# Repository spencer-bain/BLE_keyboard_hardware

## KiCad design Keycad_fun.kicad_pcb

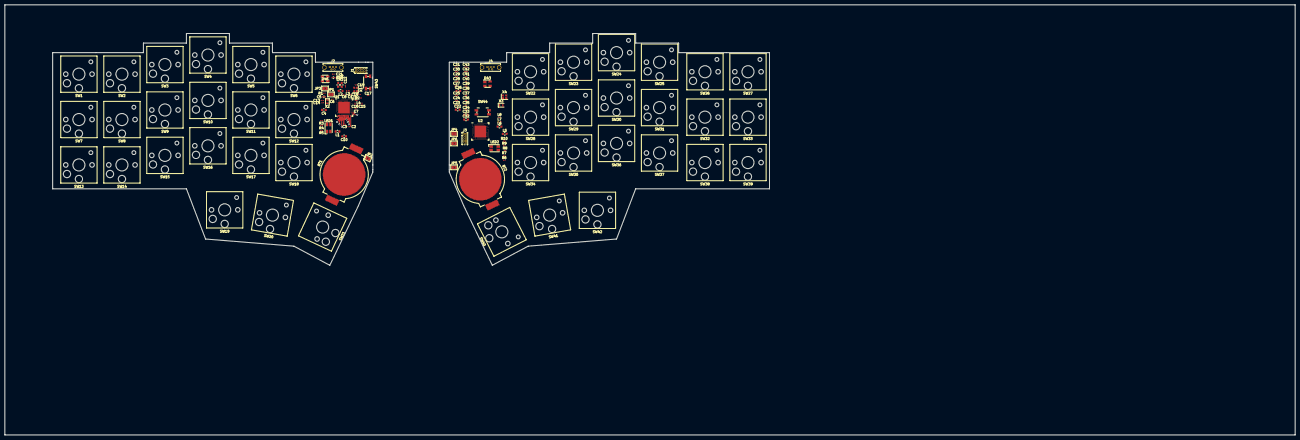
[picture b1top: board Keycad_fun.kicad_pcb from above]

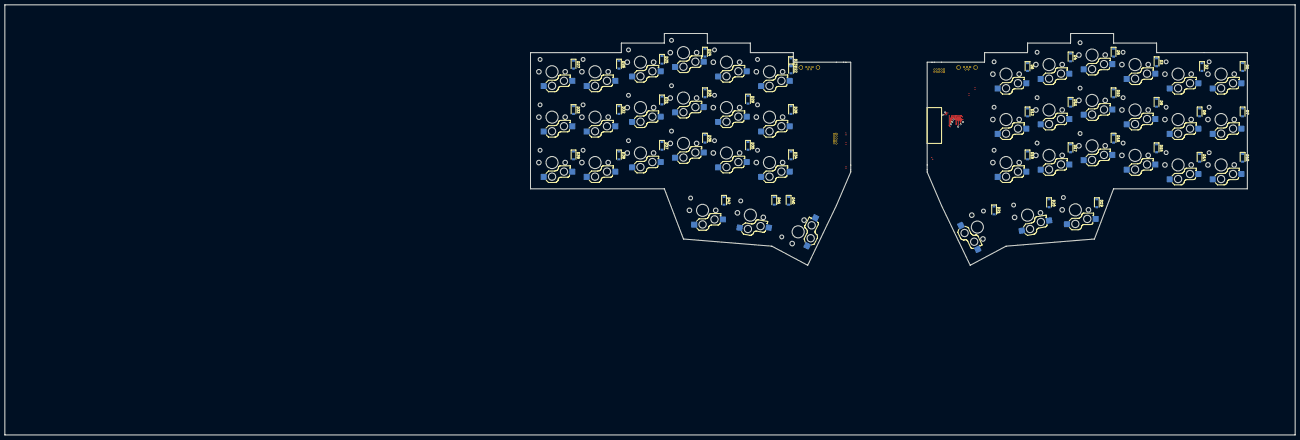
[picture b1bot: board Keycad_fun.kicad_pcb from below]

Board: 2 copper layers, 540.0 x 180.0 mm, 170 parts (42 on the bottom side), 129 nets.

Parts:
BT1, BT2: 3V; BatteryHolder_MPD_BC2003_1x2032
C0, C22: 1.0uF; C_0603_1608Metric
C1, C2, C3, C6, C17, C21, C23, C24, C25, C28, C39, C43: 100nF; C_0201_0603Metric
C4, C10, C26, C32: 4.7uF; C_0603_1608Metric
C5, C20, C27, C42: 4.7uF; C_0402_1005Metric
C7, C29: 820pF; C_0201_0603Metric
C8, C30: N.C.; C_0201_0603Metric
C9, C31: 100pF; C_0201_0603Metric
C11, C33: 1uF; C_0603_1608Metric
C12, C34: 47nF; C_0201_0603Metric
C13, C14, C18, C19, C35, C36, C40, C41: 12pF; C_0201_0603Metric
C15, C37: 0.5pF; C_0201_0603Metric
C16, C38: 0.8pF; C_0201_0603Metric
D1, D2, D3, D4, D5, D6, D7, D8, D9, D10, D11, D12, D13, D14, D15, D16, D17, D18, D19, D20, D21, D22, D23, D24, D25, D26, D27, D28, D29, D30, D31, D32, D33, D34, D35, D36, D37, D38, D39, D40, D41, D42: D; D_SOD-123
D43, D46: PRTR5V0U2X; SOT-143
J1, J3: Conn_02x05_Top_Bottom; PinHeader_2x05_P1.00mm_Vertical
J2, J4: USB_B_Micro; USB_Micro-B_Wuerth_614105150721_Vertical_CircularHoles
JP1, JP2, JP3, JP4, JP5, JP6: Jumper; SolderJumper-2_P1.3mm_Bridged2Bar_Pad1.0x1.5mm
L1, L2, L5, L6: 10uH; L_0603_1608Metric
L3, L7: 15nH; L_0402_1005Metric
L4, L8: 4.7nH; L_0201_0603Metric
LED1, LED2: ASMB-MTB0-0A3A2; LED_Avago_PLCC4_3.2x2.8mm_CW
R1, R6: 4R7; R_0201_0603Metric
R2, R10: 10k; R_0201_0603Metric
R3, R7: 1k2; R_0201_0603Metric
R4, R8: 2k2; R_0201_0603Metric
R5, R9: 390R; R_0201_0603Metric
SW1, SW2, SW3, SW4, SW5, SW6, SW7, SW8, SW9, SW10, SW11, SW12, SW13, SW14, SW15, SW16, SW17, SW18, SW19, SW20, SW21, SW22, SW23, SW24, SW25, SW26, SW27, SW28, SW29, SW30, SW31, SW32, SW33, SW34, SW35, SW36, SW37, SW38, SW39, SW40, SW41, SW42: SW_Push; SW_Hotswap_Kailh_Choc_V1V2_1.00u
SW43, SW44: SW_SPST; Panasonic_EVQPUJ_EVQPUA
U1, U2: nRF52840; Nordic_AQFN-73-1EP_7x7mm_P0.5mm
X1, X4: 32MHz; Crystal_SMD_2016-4Pin_2.0x1.6mm
X2, X3: 32.768kHz; Crystal_SMD_2012-2Pin_2.0x1.2mm

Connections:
/Col0_l: SW1.1, SW7.1, SW13.1, U1.AD8
/Col0_r: SW22.1, SW28.1, SW34.1, SW40.1, U2.AD8
/Col1_l: SW2.1, SW8.1, SW14.1, U1.AD10
/Col1_r: SW23.1, SW29.1, SW35.1, SW41.1, U2.AD10
/Col2_l: SW3.1, SW9.1, SW15.1, U1.AD12
/Col2_r: SW24.1, SW30.1, SW36.1, SW42.1, U2.AD12
/Col3_l: SW4.1, SW10.1, SW16.1, SW19.1, U1.AD16
/Col3_r: SW25.1, SW31.1, SW37.1, U2.AD16
/Col4_l: SW5.1, SW11.1, SW17.1, SW20.1, U1.AD18
/Col4_r: SW26.1, SW32.1, SW38.1, U2.AD18
/Col5_l: SW6.1, SW12.1, SW18.1, SW21.1, U1.AD20
/Col5_r: SW27.1, SW33.1, SW39.1, U2.AD20
/DCC_l: L2.2, U1.B3
/DCC_r: L6.2, U2.B3
/LED_B_l: R5.2, U1.U1
/LED_B_r: R9.2, U2.U1
/LED_G_l: R4.2, U1.R1
/LED_G_r: R8.2, U2.R1
/LED_R_l: R3.2, U1.N1
/LED_R_r: R7.2, U2.N1
/Reset_l: C17.1, R2.2, SW43.2, U1.AC13
/Reset_r: C39.1, R10.2, SW44.2, U2.AC13
/Row0_l: D1.1, D2.1, D3.1, D4.1, D5.1, D6.1, U1.L24
/Row0_r: D22.1, D23.1, D24.1, D25.1, D26.1, D27.1, U2.L24
/Row1_l: D7.1, D8.1, D9.1, D10.1, D11.1, D12.1, U1.A8
/Row1_r: D28.1, D29.1, D30.1, D31.1, D32.1, D33.1, U2.A8
/Row2_l: D13.1, D14.1, D15.1, D16.1, D17.1, D18.1, U1.A10
/Row2_r: D34.1, D35.1, D36.1, D37.1, D38.1, D39.1, U2.A10
/Row3_l: D19.1, D20.1, D21.1, U1.A12
/Row3_r: D40.1, D41.1, D42.1, U2.A12
/SWDCLK_l: J1.4, U1.AA24
/SWDCLK_r: J3.4, U2.AA24
/SWDIO_l: J1.2, U1.AC24
/SWDIO_r: J3.2, U2.AC24
/VBUS_l: C20.1, C21.1, D46.4, J1.5, JP3.2, R1.2
/VBUS_r: C42.1, C43.1, D43.4, J3.5, JP6.2, R6.2
/VDDH_l: JP1.2, U1.Y2
/VDDH_r: JP4.2, U2.Y2
/VDD_l: C0.1, C1.1, C2.1, C3.1, C4.1, JP2.2, L1.1, U1.A22, U1.AD14, U1.AD23, U1.B1, U1.W1
/VDD_r: C22.1, C23.1, C24.1, C25.1, C26.1, JP5.2, L5.1, U2.A22, U2.AD14, U2.AD23, U2.B1, U2.W1
/nrf_vcc_l: J1.1, LED1.1, R2.1
/nrf_vcc_r: J3.1, LED2.1, R10.1
GND: BT1.2, BT2.2, C0.2, C1.2, C2.2, C3.2, C4.2, C5.2, C6.1, C7.1, C8.1, C9.1, C10.1, C11.2, C12.2, C13.1, C14.1, C15.2, C16.2, C17.2, C18.2, C19.2, C20.2, C21.2, C22.2, C23.2, C24.2, C25.2, C26.2, C27.2, C28.1, C29.1, C30.1, C31.1, C32.1, C33.2, C34.2, C35.1, C36.1, C37.2, C38.2, C39.2, C40.2, C41.2, C42.2, C43.2, D43.1, D46.1, J1.3, J2.5, J3.3, J4.5, SW43.1, SW44.1, U1.B7, U1.B15, U1.EP, U1.F23, U2.B7, U2.B15, U2.EP, U2.F23, X1.2, X4.2
unnamed: BT1.1, JP2.1
unnamed: BT2.1, JP5.1
unnamed: C5.1, JP1.1, R1.1, U1.AD2
unnamed: C6.2, U1.C1
unnamed: C7.2, U1.N24
unnamed: C8.2, U1.A18
unnamed: C9.2, U1.D23
unnamed: C10.2, U1.AC5
unnamed: C11.1, L3.1, U1.B5, U1.E24
unnamed: C13.2, U1.D2, X2.1
unnamed: C14.2, U1.F2, X2.2
unnamed: C15.1, L4.1
unnamed: C16.1, L4.2, U1.H23
unnamed: C18.1, U1.B24, X1.1
unnamed: C19.1, U1.A23, X1.3
unnamed: C27.1, JP4.1, R6.1, U2.AD2
unnamed: C28.2, U2.C1
unnamed: C29.2, U2.N24
unnamed: C30.2, U2.A18
unnamed: C31.2, U2.D23
unnamed: C32.2, U2.AC5
unnamed: C33.1, L7.1, U2.B5, U2.E24
unnamed: C35.2, U2.D2, X3.1
unnamed: C36.2, U2.F2, X3.2
unnamed: C37.1, L8.1
unnamed: C38.1, L8.2, U2.H23
unnamed: C40.1, U2.B24, X4.1
unnamed: C41.1, U2.A23, X4.3
unnamed: D1.2, SW1.2
unnamed: D2.2, SW2.2
unnamed: D3.2, SW3.2
unnamed: D4.2, SW4.2
unnamed: D5.2, SW5.2
unnamed: D6.2, SW6.2
unnamed: D7.2, SW7.2
unnamed: D8.2, SW8.2
unnamed: D9.2, SW9.2
unnamed: D10.2, SW10.2
unnamed: D11.2, SW11.2
unnamed: D12.2, SW12.2
unnamed: D13.2, SW13.2
unnamed: D14.2, SW14.2
unnamed: D15.2, SW15.2
unnamed: D16.2, SW16.2
unnamed: D17.2, SW17.2
unnamed: D18.2, SW18.2
unnamed: D19.2, SW19.2
unnamed: D20.2, SW20.2
unnamed: D21.2, SW21.2
unnamed: D22.2, SW22.2
unnamed: D23.2, SW23.2
unnamed: D24.2, SW24.2
unnamed: D25.2, SW25.2
unnamed: D26.2, SW26.2
unnamed: D27.2, SW27.2
unnamed: D28.2, SW28.2
unnamed: D29.2, SW29.2
unnamed: D30.2, SW30.2
unnamed: D31.2, SW31.2
unnamed: D32.2, SW32.2
unnamed: D33.2, SW33.2
unnamed: D34.2, SW34.2
unnamed: D35.2, SW35.2
unnamed: D36.2, SW36.2
unnamed: D37.2, SW37.2
unnamed: D38.2, SW38.2
unnamed: D39.2, SW39.2
unnamed: D40.2, SW40.2
unnamed: D41.2, SW41.2
unnamed: D42.2, SW42.2
unnamed: D43.2, J4.2, U2.AD4
unnamed: D43.3, J4.3, U2.AD6
unnamed: D46.2, J2.2, U1.AD4
unnamed: D46.3, J2.3, U1.AD6
unnamed: J2.1, JP3.1
unnamed: J4.1, JP6.1
unnamed: L1.2, U1.AB2
unnamed: L2.1, L3.2
unnamed: L5.2, U2.AB2
unnamed: L6.1, L7.2
unnamed: LED1.2, R5.1
unnamed: LED1.3, R4.1
unnamed: LED1.4, R3.1
unnamed: LED2.2, R9.1
unnamed: LED2.3, R8.1
unnamed: LED2.4, R7.1

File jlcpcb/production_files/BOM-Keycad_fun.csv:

Comment,Designator,Footprint,LCSC
3V,BT1,BatteryHolder_MPD_BC2003_1x2032,
3V,BT2,BatteryHolder_MPD_BC2003_1x2032,
1.0uF,C0,C_0603_1608Metric,
100nF,C1,C_0201_0603Metric,
100nF,C2,C_0201_0603Metric,
100nF,C3,C_0201_0603Metric,
4.7uF,C4,C_0603_1608Metric,
4.7uF,C5,C_0402_1005Metric,
100nF,C6,C_0201_0603Metric,
820pF,C7,C_0201_0603Metric,
N.C.,C8,C_0201_0603Metric,
100pF,C9,C_0201_0603Metric,
4.7uF,C10,C_0603_1608Metric,
1uF,C11,C_0603_1608Metric,
47nF,C12,C_0201_0603Metric,
12pF,C13,C_0201_0603Metric,
12pF,C14,C_0201_0603Metric,
0.5pF,C15,C_0201_0603Metric,
0.8pF,C16,C_0201_0603Metric,
100nF,C17,C_0201_0603Metric,
12pF,C18,C_0201_0603Metric,
12pF,C19,C_0201_0603Metric,
4.7uF,C20,C_0402_1005Metric,
100nF,C21,C_0201_0603Metric,
1.0uF,C22,C_0603_1608Metric,
100nF,C23,C_0201_0603Metric,
100nF,C24,C_0201_0603Metric,
100nF,C25,C_0201_0603Metric,
4.7uF,C26,C_0603_1608Metric,
4.7uF,C27,C_0402_1005Metric,
100nF,C28,C_0201_0603Metric,
820pF,C29,C_0201_0603Metric,
N.C.,C30,C_0201_0603Metric,
100pF,C31,C_0201_0603Metric,
4.7uF,C32,C_0603_1608Metric,
1uF,C33,C_0603_1608Metric,
47nF,C34,C_0201_0603Metric,
12pF,C35,C_0201_0603Metric,
12pF,C36,C_0201_0603Metric,
0.5pF,C37,C_0201_0603Metric,
0.8pF,C38,C_0201_0603Metric,
100nF,C39,C_0201_0603Metric,
12pF,C40,C_0201_0603Metric,
12pF,C41,C_0201_0603Metric,
4.7uF,C42,C_0402_1005Metric,
100nF,C43,C_0201_0603Metric,
PRTR5V0U2X,D43,SOT-143,
PRTR5V0U2X,D46,SOT-143,
Conn_02x05_Top_Bottom,J1,PinHeader_2x05_P1.00mm_Vertical,
USB_B_Micro,J2,USB_Micro-B_Wuerth_614105150721_Vertical_CircularHoles,
Conn_02x05_Top_Bottom,J3,PinHeader_2x05_P1.00mm_Vertical,
USB_B_Micro,J4,USB_Micro-B_Wuerth_614105150721_Vertical_CircularHoles,
Jumper,JP1,SolderJumper-2_P1.3mm_Open_Pad1.0x1.5mm,
Jumper,JP2,SolderJumper-2_P1.3mm_Open_Pad1.0x1.5mm,
Jumper,JP3,SolderJumper-2_P1.3mm_Open_Pad1.0x1.5mm,
Jumper,JP4,SolderJumper-2_P1.3mm_Open_Pad1.0x1.5mm,
Jumper,JP5,SolderJumper-2_P1.3mm_Open_Pad1.0x1.5mm,
Jumper,JP6,SolderJumper-2_P1.3mm_Open_Pad1.0x1.5mm,
10uH,L1,L_0603_1608Metric,
10uH,L2,L_0603_1608Metric,
15nH,L3,L_0402_1005Metric,
4.7nH,L4,L_0201_0603Metric,
10uH,L5,L_0603_1608Metric,
10uH,L6,L_0603_1608Metric,
15nH,L7,L_0402_1005Metric,
4.7nH,L8,L_0201_0603Metric,
ASMB-MTB0-0A3A2,LED1,LED_Avago_PLCC4_3.2x2.8mm_CW,
ASMB-MTB0-0A3A2,LED2,LED_Avago_PLCC4_3.2x2.8mm_CW,
4R7,R1,R_0201_0603Metric,
10k,R2,R_0201_0603Metric,
1k2,R3,R_0201_0603Metric,
2k2,R4,R_0201_0603Metric,
390R,R5,R_0201_0603Metric,
4R7,R6,R_0201_0603Metric,
1k2,R7,R_0201_0603Metric,
2k2,R8,R_0201_0603Metric,
390R,R9,R_0201_0603Metric,
10k,R10,R_0201_0603Metric,
SW_Push,SW1,SW_Hotswap_Kailh_Choc_V1V2_1.00u,
SW_Push,SW2,SW_Hotswap_Kailh_Choc_V1V2_1.00u,
SW_Push,SW3,SW_Hotswap_Kailh_Choc_V1V2_1.00u,
SW_Push,SW4,SW_Hotswap_Kailh_Choc_V1V2_1.00u,
SW_Push,SW5,SW_Hotswap_Kailh_Choc_V1V2_1.00u,
SW_Push,SW6,SW_Hotswap_Kailh_Choc_V1V2_1.00u,
SW_Push,SW7,SW_Hotswap_Kailh_Choc_V1V2_1.00u,
SW_Push,SW8,SW_Hotswap_Kailh_Choc_V1V2_1.00u,
SW_Push,SW9,SW_Hotswap_Kailh_Choc_V1V2_1.00u,
SW_Push,SW10,SW_Hotswap_Kailh_Choc_V1V2_1.00u,
SW_Push,SW11,SW_Hotswap_Kailh_Choc_V1V2_1.00u,
SW_Push,SW12,SW_Hotswap_Kailh_Choc_V1V2_1.00u,
SW_Push,SW13,SW_Hotswap_Kailh_Choc_V1V2_1.00u,
SW_Push,SW14,SW_Hotswap_Kailh_Choc_V1V2_1.00u,
SW_Push,SW15,SW_Hotswap_Kailh_Choc_V1V2_1.00u,
SW_Push,SW16,SW_Hotswap_Kailh_Choc_V1V2_1.00u,
SW_Push,SW17,SW_Hotswap_Kailh_Choc_V1V2_1.00u,
SW_Push,SW18,SW_Hotswap_Kailh_Choc_V1V2_1.00u,
SW_Push,SW19,SW_Hotswap_Kailh_Choc_V1V2_1.00u,
SW_Push,SW20,SW_Hotswap_Kailh_Choc_V1V2_1.00u,
SW_Push,SW21,SW_Hotswap_Kailh_Choc_V1V2_1.00u,
SW_Push,SW22,SW_Hotswap_Kailh_Choc_V1V2_1.00u,
SW_Push,SW23,SW_Hotswap_Kailh_Choc_V1V2_1.00u,
SW_Push,SW24,SW_Hotswap_Kailh_Choc_V1V2_1.00u,
SW_Push,SW25,SW_Hotswap_Kailh_Choc_V1V2_1.00u,
SW_Push,SW26,SW_Hotswap_Kailh_Choc_V1V2_1.00u,
SW_Push,SW27,SW_Hotswap_Kailh_Choc_V1V2_1.00u,
SW_Push,SW28,SW_Hotswap_Kailh_Choc_V1V2_1.00u,
SW_Push,SW29,SW_Hotswap_Kailh_Choc_V1V2_1.00u,
SW_Push,SW30,SW_Hotswap_Kailh_Choc_V1V2_1.00u,
SW_Push,SW31,SW_Hotswap_Kailh_Choc_V1V2_1.00u,
SW_Push,SW32,SW_Hotswap_Kailh_Choc_V1V2_1.00u,
SW_Push,SW33,SW_Hotswap_Kailh_Choc_V1V2_1.00u,
SW_Push,SW34,SW_Hotswap_Kailh_Choc_V1V2_1.00u,
SW_Push,SW35,SW_Hotswap_Kailh_Choc_V1V2_1.00u,
SW_Push,SW36,SW_Hotswap_Kailh_Choc_V1V2_1.00u,
SW_Push,SW37,SW_Hotswap_Kailh_Choc_V1V2_1.00u,
SW_Push,SW38,SW_Hotswap_Kailh_Choc_V1V2_1.00u,
SW_Push,SW39,SW_Hotswap_Kailh_Choc_V1V2_1.00u,
SW_Push,SW40,SW_Hotswap_Kailh_Choc_V1V2_1.00u,
SW_Push,SW41,SW_Hotswap_Kailh_Choc_V1V2_1.00u,
SW_Push,SW42,SW_Hotswap_Kailh_Choc_V1V2_1.00u,
SW_SPST,SW43,Panasonic_EVQPUJ_EVQPUA,
SW_SPST,SW44,Panasonic_EVQPUJ_EVQPUA,
nRF52840,U1,Nordic_AQFN-73-1EP_7x7mm_P0.5mm,
nRF52840,U2,Nordic_AQFN-73-1EP_7x7mm_P0.5mm,
32MHz,X1,Crystal_SMD_2016-4Pin_2.0x1.6mm,
32.768kHz,X2,Crystal_SMD_2012-2Pin_2.0x1.2mm,
32.768kHz,X3,Crystal_SMD_2012-2Pin_2.0x1.2mm,
32MHz,X4,Crystal_SMD_2016-4Pin_2.0x1.6mm,
D,D1,D_SOD-123,
D,D2,D_SOD-123,
D,D3,D_SOD-123,
D,D4,D_SOD-123,
D,D5,D_SOD-123,
D,D6,D_SOD-123,
D,D7,D_SOD-123,
D,D8,D_SOD-123,
D,D9,D_SOD-123,
D,D10,D_SOD-123,
D,D11,D_SOD-123,
D,D12,D_SOD-123,
D,D13,D_SOD-123,
D,D14,D_SOD-123,
D,D15,D_SOD-123,
D,D16,D_SOD-123,
D,D17,D_SOD-123,
D,D18,D_SOD-123,
D,D19,D_SOD-123,
D,D20,D_SOD-123,
D,D21,D_SOD-123,
D,D22,D_SOD-123,
D,D23,D_SOD-123,
D,D24,D_SOD-123,
D,D25,D_SOD-123,
D,D26,D_SOD-123,
D,D27,D_SOD-123,
D,D28,D_SOD-123,
D,D29,D_SOD-123,
D,D30,D_SOD-123,
D,D31,D_SOD-123,
D,D32,D_SOD-123,
D,D33,D_SOD-123,
D,D34,D_SOD-123,
D,D35,D_SOD-123,
D,D36,D_SOD-123,
D,D37,D_SOD-123,
D,D38,D_SOD-123,
D,D39,D_SOD-123,
D,D40,D_SOD-123,
D,D41,D_SOD-123,
D,D42,D_SOD-123,

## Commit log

2023-05-24 Making some more general prosses
